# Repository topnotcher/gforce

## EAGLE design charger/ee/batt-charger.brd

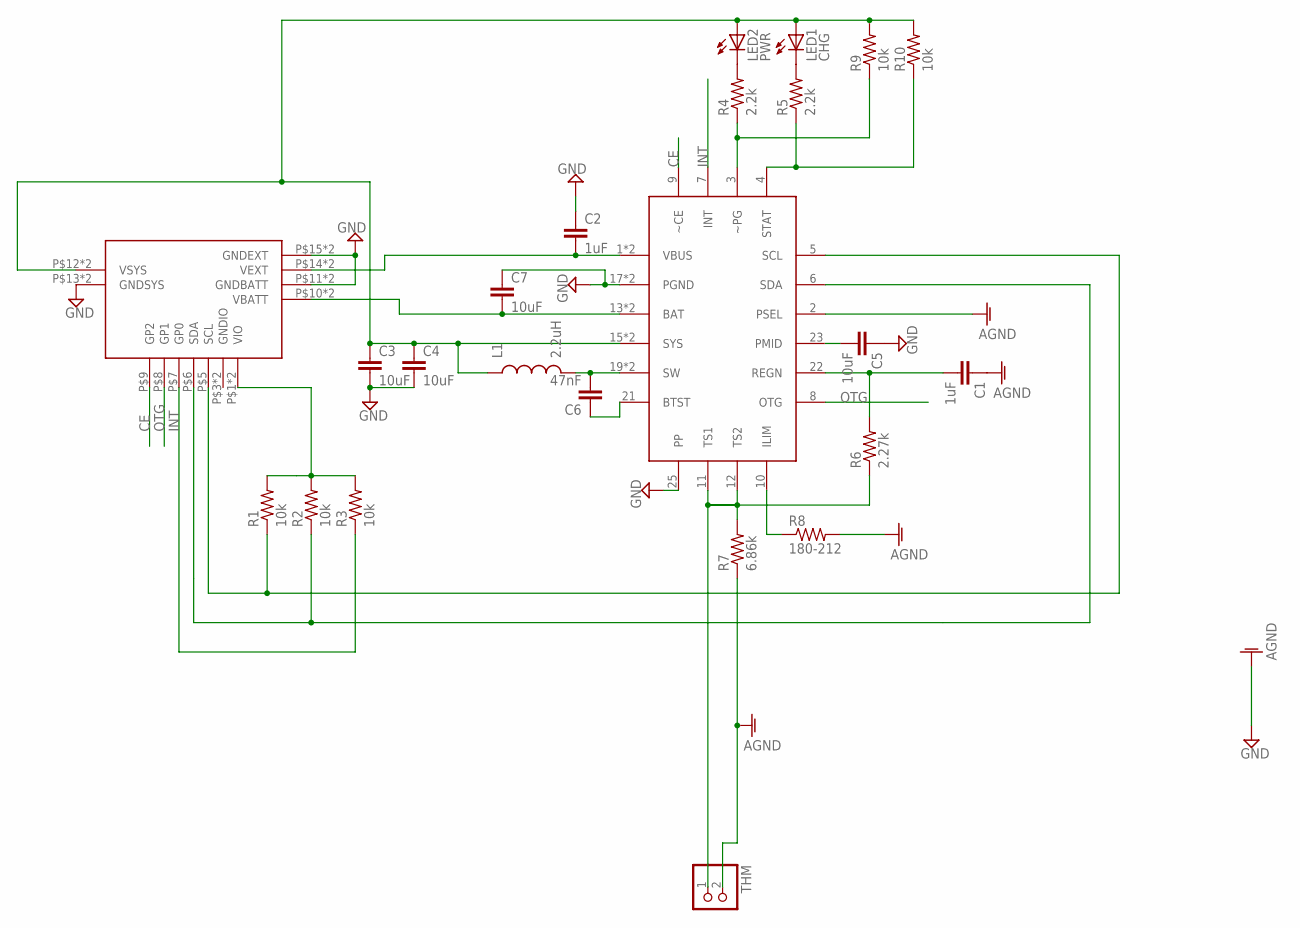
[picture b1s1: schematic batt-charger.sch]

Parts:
C1, C2: 1uF; 0603-CAP
C3, C4, C5, C7: 10uF; 1206
C6: 47nF; 0603-CAP
L1: 2.2uH; INDUCTOR-2020
LED1: CHG; CHIP-LED0603
LED2: PWR; CHIP-LED0603
R1, R2, R3, R9, R10: 10k; R0603
R4, R5: 2.2k; R0603
R6: 2.27k; R0603
R7: 6.86k; R0603
R8: 180-212; R0603
THM: JST_2PIN-THM; JST-PH-2-THM
U$1: BQ24193; QFN-400X400X100-25P
U$2: G4-CHG-SOCKETSTD; G4-CHG-SOCKET

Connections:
AGND: C1.1, R7.1, R8.2, THM.2 (1), U$1.2 (PSEL)
CE: U$1.9 (~CE), U$2.P$9 (GP2)
GND: C2.1, C3.2, C4.2, C5.1, C7.1, U$1.17 (PGND), U$1.18 (PGND), U$1.25 (PP), U$2.P$11 (GNDBATT), U$2.P$13 (GNDSYS), U$2.P$15 (GNDEXT), U$2.P$17 (GNDBATT), U$2.P$19 (GNDSYS), U$2.P$21 (GNDEXT)
INT: R3.1, U$1.7 (INT), U$2.P$7 (GP0)
unnamed: C6.2, L1.P$2 (2), U$1.19 (SW), U$1.20 (SW)
unnamed: R1.1, U$1.5 (SCL), U$2.P$5 (SCL)
unnamed: R2.1, U$1.6 (SDA), U$2.P$6 (SDA)
unnamed: C6.1, U$1.21 (BTST)
unnamed: LED2.C, R4.2
unnamed: LED1.C, R5.2
unnamed: R4.1, R9.1, U$1.3 (~PG)
unnamed: R5.1, R10.1, U$1.4 (STAT)
unnamed: C1.2, R6.2, U$1.22 (REGN)
unnamed: R6.1, R7.2, THM.1 (2), U$1.11 (TS1), U$1.12 (TS2)
unnamed: R8.1, U$1.10 (ILIM)
unnamed: C5.2, U$1.23 (PMID)
OTG: U$1.8 (OTG), U$2.P$8 (GP1)
VBATT: C7.2, U$1.13 (BAT), U$1.14 (BAT), U$2.P$10 (VBATT), U$2.P$16 (VBATT)
VEXT: C2.2, U$1.1 (VBUS), U$1.24 (VBUS), U$2.P$14 (VEXT), U$2.P$20 (VEXT)
VIO: R1.2, R2.2, R3.2, U$2.P$1 (VIO), U$2.P$2 (VIO)
VSYS: C3.1, C4.1, L1.P$1 (1), LED1.A, LED2.A, R9.2, R10.2, U$1.15 (SYS), U$1.16 (SYS), U$2.P$12 (VSYS), U$2.P$18 (VSYS)

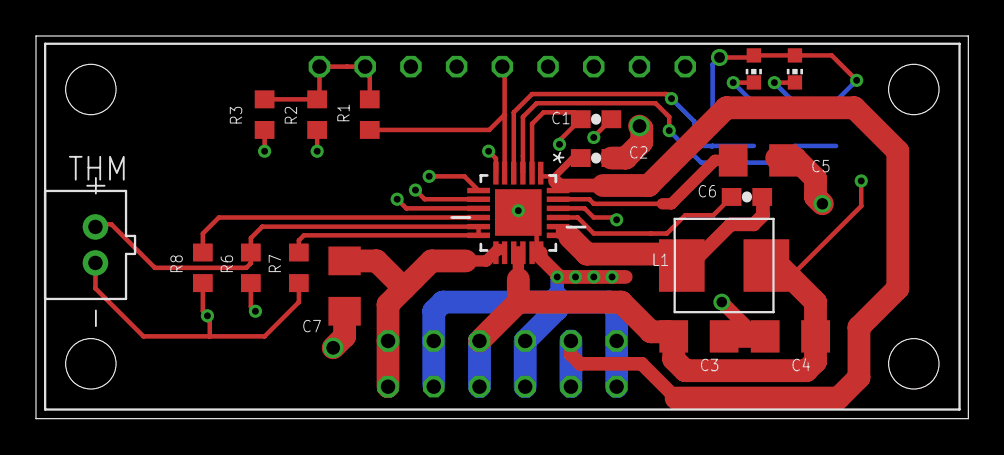
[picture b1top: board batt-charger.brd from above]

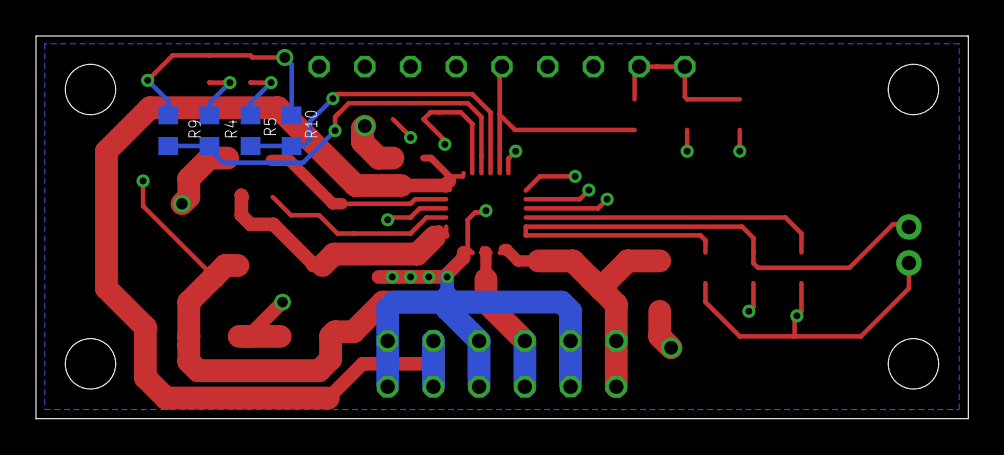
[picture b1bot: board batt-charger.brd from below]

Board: 4 copper layers, 51.8 x 21.3 mm, 23 parts (4 on the bottom side), 21 nets.

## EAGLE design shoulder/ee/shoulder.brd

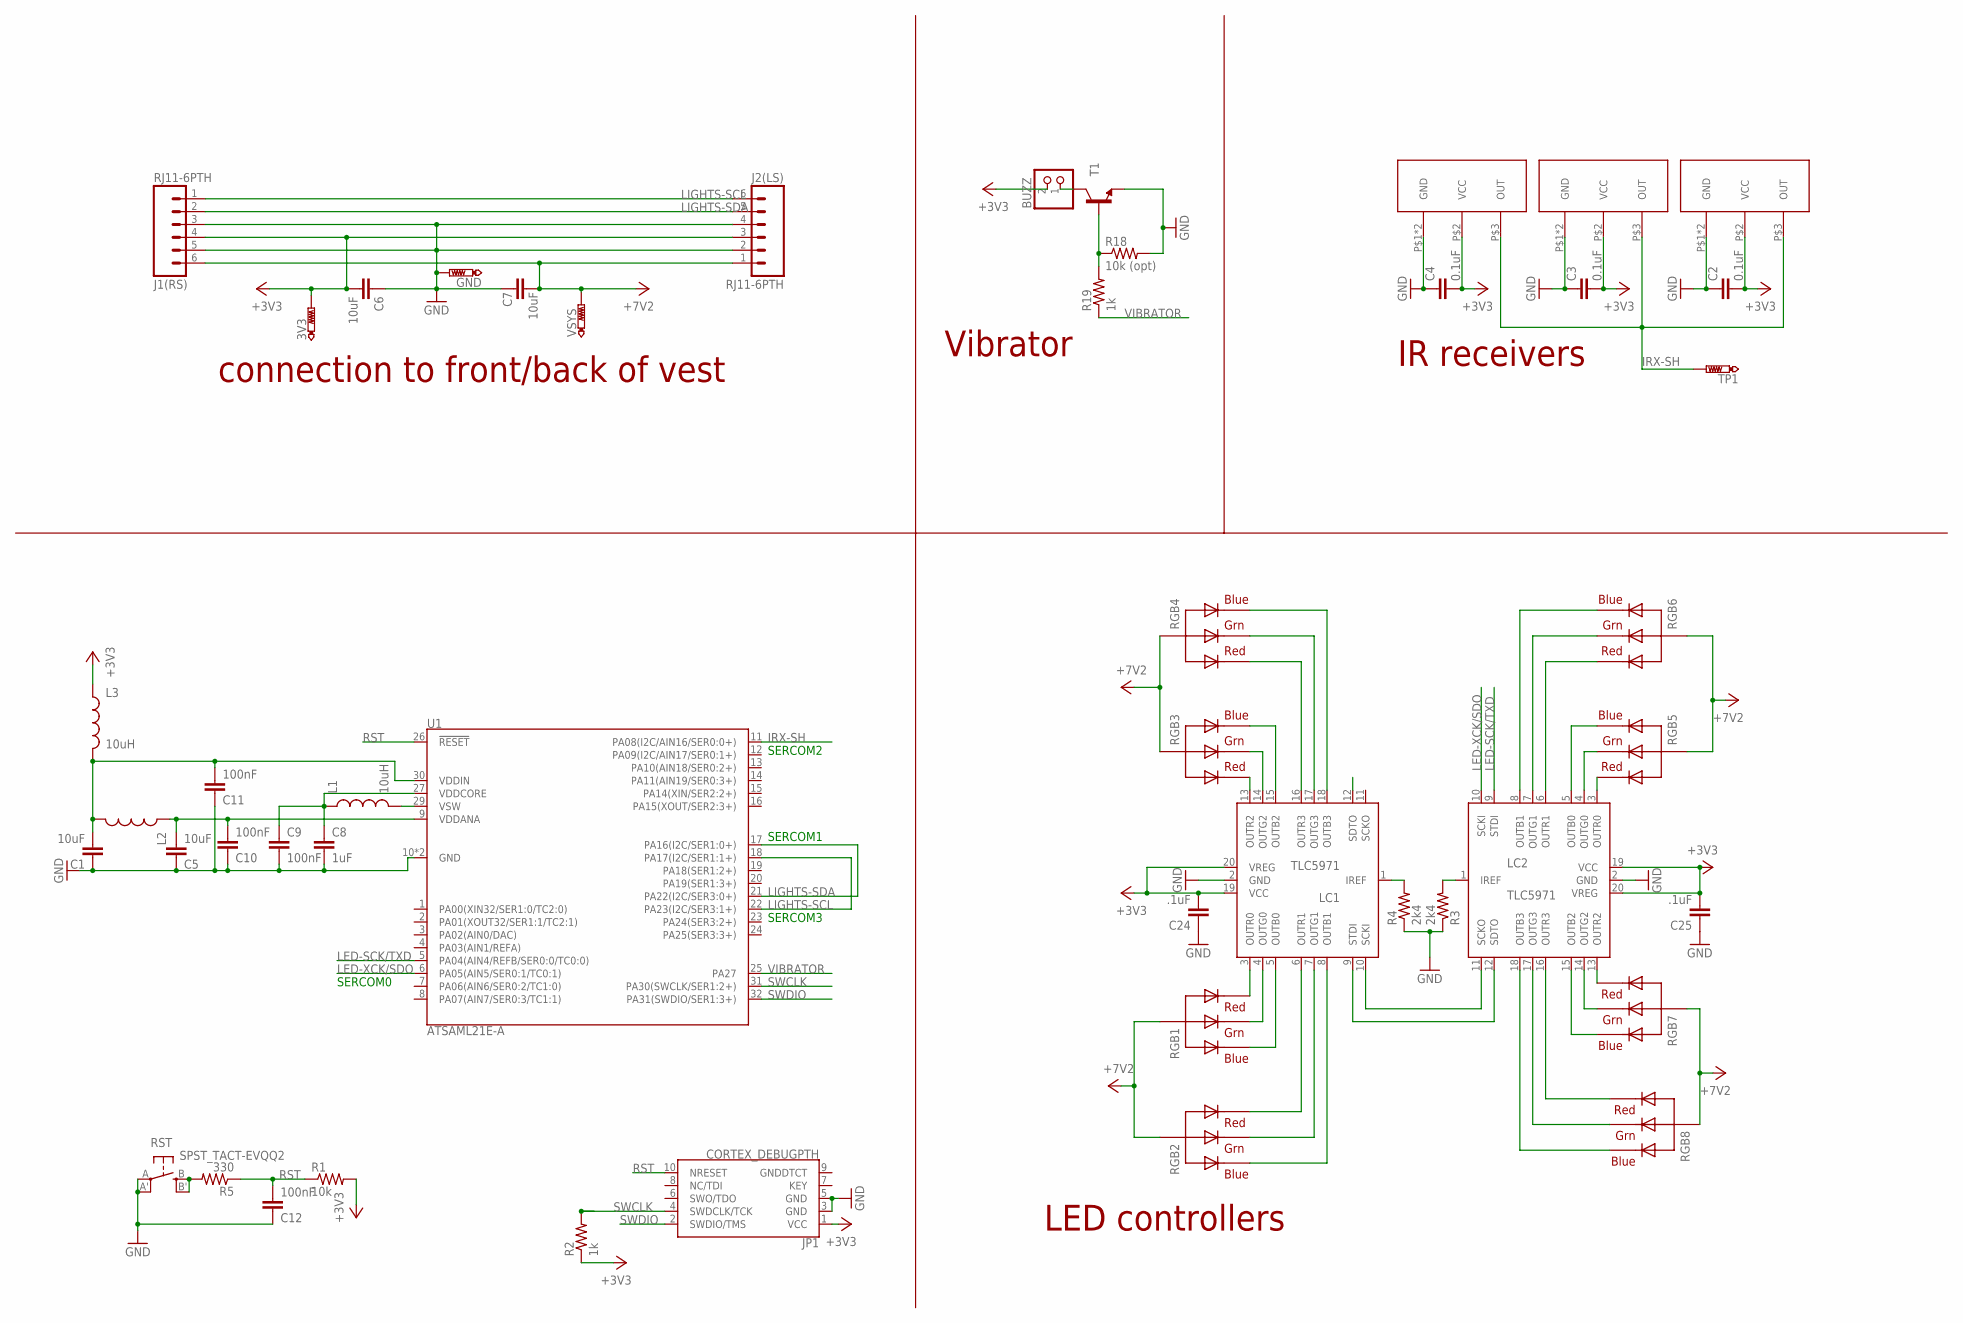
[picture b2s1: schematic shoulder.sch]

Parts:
3V3: PTR1PAD1-17; P1-17
BUZZ: JST_2PIN-THM; JST-PH-2-THM
C1, C5: 10uF; 0603-CAP
C2, C3, C4: 0.1uF; 0603-CAP
C6, C7: 10uF; 1206
C8: 1uF; 0603-CAP
C9, C10, C11, C12: 100nF; 0603-CAP
C24, C25: .1uF; 0603-CAP
GND: PTR1PAD1-17; P1-17
J1(RS), J2(LS): RJ11-6PTH; RJ11-6
JP1: CORTEX_DEBUGPTH; 2X5-PTH-1.27MM
L1, L3: 10uH; 0805
L2: INDUCTOR0603; 0603
LC1, LC2: TLC5971; SSOP20
R1: 10k; 0603-RES
R2, R19: 1k; 0603-RES
R3, R4: 2k4; 0603-RES
R5: 330; 0603-RES
R18: 10k (opt); 0603-RES
RGB1, RGB2, RGB3, RGB4, RGB5, RGB6, RGB7, RGB8: AVAGO-RGB-SMT; AVAGO-SMT-RGB
RST: SPST_TACT-EVQQ2; EVQ-Q2
T1: TRANSISTOR_NPNSOT23; SOT23
TP1: PTR1PAD1-17; P1-17
U1: ATSAML21E-A; TQFP-32-7X7-0.8MM
U$1, U$2: TSMP77000SIDE; TSMP77000
U$3: TSMP77000UP; HEIMDALL-UP
VSYS: PTR1PAD1-17; P1-17

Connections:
+3V3: 3V3.TP, BUZZ.2 (1), C2.2, C3.2, C4.2, C6.2, C24.2, C25.2, J1(RS).4, J2(LS).3, JP1.1 (VCC), L3.1, LC1.19 (VCC), LC1.20 (VREG), LC2.19 (VCC), LC2.20 (VREG), R1.2, R2.1, U$1.P$2 (VCC), U$2.P$2 (VCC), U$3.P$2 (VCC)
+7V2: C7.2, J1(RS).6, J2(LS).1, RGB1.P$4 (VCC), RGB1.P$5 (VCC), RGB1.P$6 (VCC), RGB2.P$4 (VCC), RGB2.P$5 (VCC), RGB2.P$6 (VCC), RGB3.P$4 (VCC), RGB3.P$5 (VCC), RGB3.P$6 (VCC), RGB4.P$4 (VCC), RGB4.P$5 (VCC), RGB4.P$6 (VCC), RGB5.P$4 (VCC), RGB5.P$5 (VCC), RGB5.P$6 (VCC), RGB6.P$4 (VCC), RGB6.P$5 (VCC), RGB6.P$6 (VCC), RGB7.P$4 (VCC), RGB7.P$5 (VCC), RGB7.P$6 (VCC), RGB8.P$4 (VCC), RGB8.P$5 (VCC), RGB8.P$6 (VCC), VSYS.TP
GND: C1.1, C2.1, C3.1, C4.1, C5.1, C6.1, C7.1, C8.2, C9.2, C10.1, C11.1, C12.1, C24.1, C25.1, GND.TP, J1(RS).3, J1(RS).5, J2(LS).2, J2(LS).4, JP1.3 (GND), JP1.5 (GND), LC1.2 (GND), LC2.2 (GND), R3.1, R4.1, R18.2, RST.A, RST.A' (P1), T1.2 (E), U1.10 (GND), U1.28 (GND), U$1.P$1 (GND), U$1.P$4 (GND), U$2.P$1 (GND), U$2.P$4 (GND), U$3.P$1 (GND), U$3.P$4 (GND)
IRX-SH: TP1.TP, U1.11 (PA08(I2C/AIN16/SER0:0+)), U$1.P$3 (OUT), U$2.P$3 (OUT), U$3.P$3 (OUT)
LED-SCK/TXD: LC2.9 (STDI), U1.5 (PA04(AIN4/REFB/SER0:0/TC0:0))
LED-XCK/SDO: LC2.10 (SCKI), U1.6 (PA05(AIN5/SER0:1/TC0:1))
LIGHTS-SCL: J1(RS).1, J2(LS).6, U1.18 (PA17(I2C/SER1:1+)), U1.22 (PA23(I2C/SER3:1+))
LIGHTS-SDA: J1(RS).2, J2(LS).5, U1.17 (PA16(I2C/SER1:0+)), U1.21 (PA22(I2C/SER3:0+))
unnamed: LC1.10 (SCKI), LC2.11 (SCKO)
unnamed: LC1.9 (STDI), LC2.12 (SDTO)
unnamed: C5.2, C10.2, L2.1, U1.9 (VDDANA)
unnamed: C1.2, C11.2, L2.2, L3.2, U1.30 (VDDIN)
unnamed: R5.2, RST.B (S), RST.B' (S1)
unnamed: L1.2, U1.29 (VSW)
unnamed: LC1.3 (OUTR0), RGB1.P$3 (RED)
unnamed: LC2.3 (OUTR0), RGB5.P$3 (RED)
unnamed: LC2.6 (OUTR1), RGB6.P$3 (RED)
unnamed: C8.1, C9.1, L1.1, U1.27 (VDDCORE)
unnamed: BUZZ.1 (2), T1.3 (C)
unnamed: LC1.15 (OUTB2), RGB3.P$1 (BLUE)
unnamed: R18.1, R19.2, T1.1 (B)
unnamed: LC1.13 (OUTR2), RGB3.P$3 (RED)
unnamed: LC1.14 (OUTG2), RGB3.P$2 (GREEN)
unnamed: LC1.16 (OUTR3), RGB4.P$3 (RED)
unnamed: LC1.17 (OUTG3), RGB4.P$2 (GREEN)
unnamed: LC1.18 (OUTB3), RGB4.P$1 (BLUE)
unnamed: LC1.4 (OUTG0), RGB1.P$2 (GREEN)
unnamed: LC1.5 (OUTB0), RGB1.P$1 (BLUE)
unnamed: LC1.6 (OUTR1), RGB2.P$3 (RED)
unnamed: LC1.7 (OUTG1), RGB2.P$2 (GREEN)
unnamed: LC1.8 (OUTB1), RGB2.P$1 (BLUE)
unnamed: LC2.4 (OUTG0), RGB5.P$2 (GREEN)
unnamed: LC2.5 (OUTB0), RGB5.P$1 (BLUE)
unnamed: LC2.7 (OUTG1), RGB6.P$2 (GREEN)
unnamed: LC2.8 (OUTB1), RGB6.P$1 (BLUE)
unnamed: LC2.16 (OUTR3), RGB8.P$3 (RED)
unnamed: LC2.17 (OUTG3), RGB8.P$2 (GREEN)
unnamed: LC2.18 (OUTB3), RGB8.P$1 (BLUE)
unnamed: LC2.15 (OUTB2), RGB7.P$1 (BLUE)
unnamed: LC2.14 (OUTG2), RGB7.P$2 (GREEN)
unnamed: LC2.13 (OUTR2), RGB7.P$3 (RED)
unnamed: LC1.1 (IREF), R4.2
unnamed: LC2.1 (IREF), R3.2
RST: C12.2, JP1.10 (NRESET), R1.1, R5.1, U1.26 (!RESET!)
SWCLK: JP1.4 (SWDCLK/TCK), R2.2, U1.31 (PA30(SWCLK/SER1:2+))
SWDIO: JP1.2 (SWDIO/TMS), U1.32 (PA31(SWDIO/SER1:3+))
VIBRATOR: R19.1, U1.25 (PA27)

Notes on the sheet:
connection to front/back of vest
IR receivers
Vibrator
LED controllers
SERCOM0
SERCOM3
SERCOM1
SERCOM2

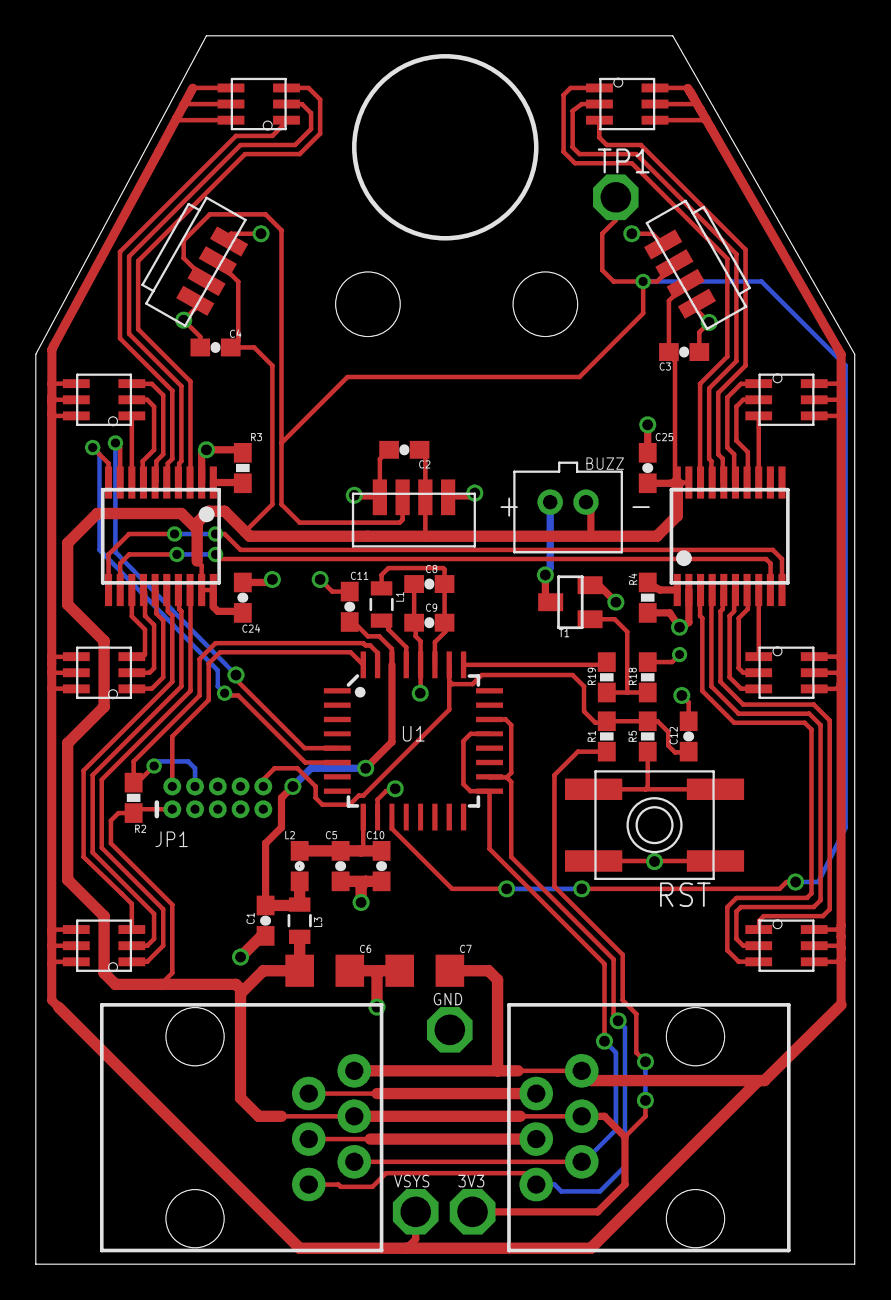
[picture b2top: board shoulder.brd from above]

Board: 2 copper layers, 45.7 x 68.6 mm, 48 parts (0 on the bottom side), 47 nets.

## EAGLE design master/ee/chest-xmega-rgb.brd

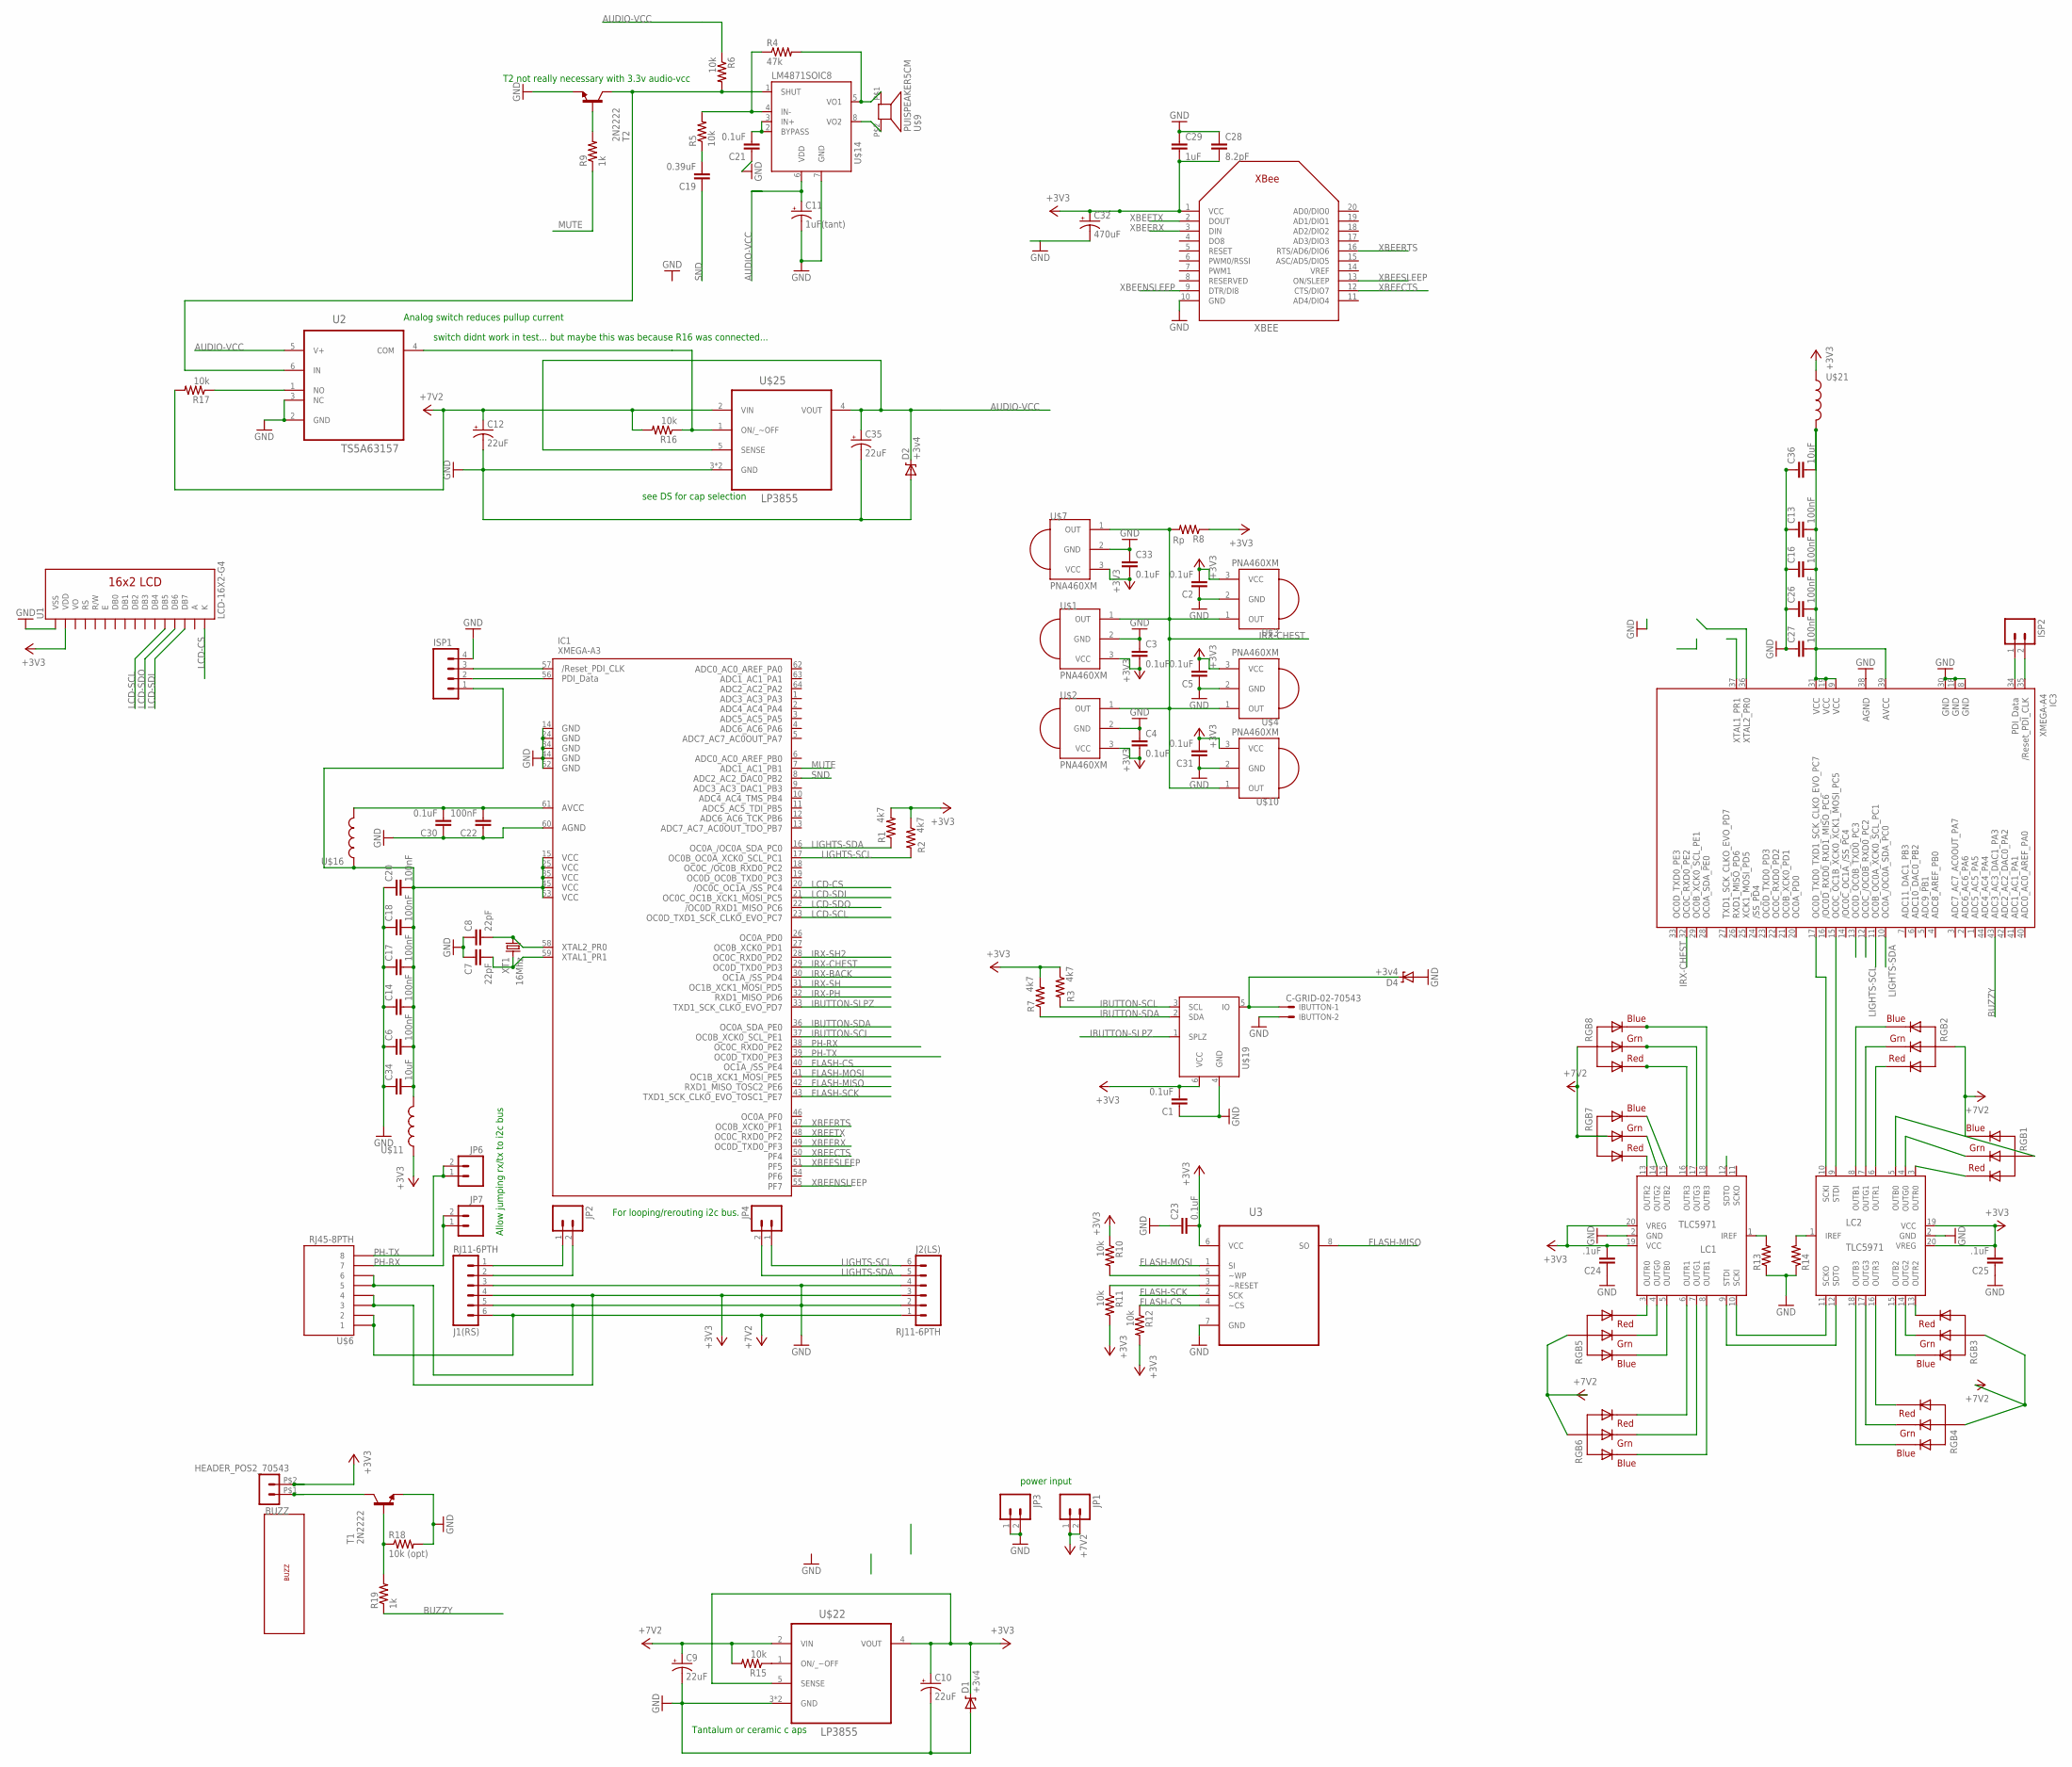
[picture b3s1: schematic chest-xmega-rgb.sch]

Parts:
BUZZ: HEADER_POS2_70543; 70543-POS2
C1, C23, C30: 0.1uF; 0603-CAP
C2, C3, C4, C5, C21, C31, C33: 0.1uF; CAP-PTH-SMALL
C6, C13, C14, C16, C17, C18, C20, C22, C26, C27: 100nF; 0603-CAP
C7, C8: 22pF; CAP-PTH-SMALL
C9, C10, C12, C35: 22uF; EIA3216
C11: 1uF(tant); EIA3216
C19: 0.39uF; CAP-PTH-SMALL
C24, C25: .1uF; CAP-PTH-SMALL
C28: 8.2pF; 0603-CAP
C29: 1uF; 0603-CAP
C32: 470uF; PANASONIC_E
C34, C36: 10uF; 1206
D1, D2, D4: +3v4; DIODE-ZENER
IBUTTON: C-GRID-02-70543; 70543-02
IC1: XMEGA-A3; TQFP64
IC3: XMEGA-A4; TQFP44
ISP1: M04LOCK; 1X04_LOCK
ISP2: M02LOCK; 1X02_LOCK
J1(RS), J2(LS): RJ11-6PTH; RJ11-6
JP1, JP3: M023.5MM; SCREWTERMINAL-3.5MM-2
JP2, JP4, JP6, JP7: M02LOCK; 1X02_LOCK
LC1, LC2: TLC5971; SSOP20
R1, R2, R3, R7: 4k7; 0204/7
R4: 47k; 0204/7
R5, R6, R15, R16, R17: 10k; 0204/7
R8: Rp; 0204/7
R9, R19: 1k; 0204/7
R10, R11, R12: 10k; 0805
R13, R14: R-US_0204/7; 0204/7
R18: 10k (opt); 0204/7
RGB1, RGB2, RGB3, RGB4, RGB5, RGB6, RGB7, RGB8: AVAGO-RGB-SMT; AVAGO-SMT-RGB
T1, T2: 2N2222; TO92-EBC-OVAL
U1: LCD-16X2-G4
U2: TS5A63157; SOT65P210X110-6N
U3: AT45DB321D-SU; SOIC127P798X216-8N
U$1, U$2, U$3, U$4, U$7, U$10: PNA460XM
U$6: RJ45-8PTH; RJ45-8
U$9: PUISPEAKER5CM; PUI-AS05008MR-4-R
U$11, U$16, U$21: INDUCTOR1206H*; 1206
U$13: VIB-CAPSULE
U$14: LM4871SOIC8; SOIC8
U$19: DS2483-SOT23-6; SOT23-6
U$22, U$25: LP3855; TO-263-5
XBEE: XBEE-WIFIXBEE; XBEE-WIFI
XT1: 16Mhz; HC49US

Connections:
+3V3: BUZZ.P$2 (2), C1.2, C2.2, C3.2, C4.2, C5.2, C10.A (+), C23.2, C24.2, C25.2, C28.2, C29.2, C31.2, C32.+, C33.2, D1.P$1 (C), J1(RS).4, J2(LS).3, LC1.19 (VCC), LC1.20 (VREG), LC2.19 (VCC), LC2.20 (VREG), R1.2, R2.1, R3.1, R7.2, R8.1, R10.1, R11.2, R12.2, U1.2 (VDD), U3.6 (VCC), U$1.3 (VCC), U$2.3 (VCC), U$3.3 (VCC), U$4.3 (VCC), U$6.3, U$6.4, U$7.3 (VCC), U$10.3 (VCC), U$11.1, U$19.6 (VCC), U$21.1, U$22.4 (VOUT), U$22.5 (SENSE), XBEE.1 (VCC)
+7V2: C9.A (+), C12.A (+), J1(RS).6, J2(LS).1, JP1.1, JP1.2, R15.2, R16.2, R17.2, RGB1.P$4 (VCC), RGB1.P$5 (VCC), RGB1.P$6 (VCC), RGB2.P$4 (VCC), RGB2.P$5 (VCC), RGB2.P$6 (VCC), RGB4.P$4 (VCC), RGB4.P$5 (VCC), RGB4.P$6 (VCC), RGB5.P$4 (VCC), RGB5.P$5 (VCC), RGB5.P$6 (VCC), RGB6.P$4 (VCC), RGB6.P$5 (VCC), RGB6.P$6 (VCC), RGB7.P$4 (VCC), RGB7.P$5 (VCC), RGB7.P$6 (VCC), RGB8.P$4 (VCC), RGB8.P$5 (VCC), RGB8.P$6 (VCC), U$6.1, U$6.2, U$22.2 (VIN), U$25.2 (VIN)
A: U1.15 (A)
AUDIO-VCC: C11.A (+), C35.A (+), D2.P$1 (C), R6.1, U2.5 (V+), U$14.6 (VDD), U$25.4 (VOUT), U$25.5 (SENSE)
BUZZY: IC3.43 (PA3), R19.1
FLASH-CS: IC1.40 (PE4), R12.1, U3.4 (~CS)
FLASH-MISO: IC1.42 (PE6), U3.8 (SO)
FLASH-MOSI: IC1.41 (PE5), U3.1 (SI)
FLASH-SCK: IC1.43 (PE7), U3.2 (SCK)
GND: C1.1, C2.1, C3.1, C4.1, C5.1, C6.1, C7.1, C8.1, C9.C (-), C10.C (-), C11.C (-), C12.C (-), C13.1, C14.1, C16.1, C17.1, C18.1, C20.1, C21.1, C22.1, C23.1, C24.1, C25.1, C26.1, C27.1, C28.1, C29.1, C30.1, C31.1, C32.-, C33.1, C34.1, C35.C (-), C36.1, D1.P$2 (A), D2.P$2 (A), D4.P$2 (A), IBUTTON.2, IC1.14 (GND1), IC1.24 (GND2), IC1.34 (GND3), IC1.44 (GND4), IC1.52 (GND5), IC1.60 (AGND), IC3.8 (GND1), IC3.18 (GND2), IC3.30 (GND3), IC3.38 (AGND), ISP1.4, J1(RS).3, J1(RS).5, J2(LS).2, J2(LS).4, JP3.1, JP3.2, LC1.2 (GND), LC2.2 (GND), R13.1, R14.1, R18.2, T1.E, T2.E, U1.1 (VSS), U2.2 (GND), U2.3 (NC), U3.7 (GND), U$1.2 (GND), U$2.2 (GND), U$3.2 (GND), U$4.2 (GND), U$6.5, U$6.6, U$7.2 (GND), U$10.2 (GND), U$14.7 (GND), U$19.4 (GND), U$22.3 (GND), U$22.TAB (GND), U$25.3 (GND), U$25.TAB (GND), XBEE.10 (GND)
IBUTTON-SCL: IC1.37 (PE1), R3.2, U$19.3 (SCL)
IBUTTON-SDA: IC1.36 (PE0), R7.1, U$19.2 (SDA)
IBUTTON-SLPZ: IC1.33 (PD7), U$19.1 (SPLZ)
IRX-BACK: IC1.30 (PD4)
IRX-CHEST: IC1.29 (PD3), IC3.32 (PE2), R8.2, U$1.1 (OUT), U$2.1 (OUT), U$3.1 (OUT), U$4.1 (OUT), U$7.1 (OUT), U$10.1 (OUT)
IRX-PH: IC1.32 (PD6)
IRX-SH: IC1.31 (PD5)
IRX-SH2: IC1.28 (PD2)
LCD-CS: IC1.20 (PC4), U1.16 (K)
LCD-SCL: IC1.23 (PC7), U1.12 (DB5)
LCD-SDI: IC1.21 (PC5), U1.14 (DB7)
LCD-SDO: IC1.22 (PC6), U1.13 (DB6)
LIGHTS-SCL: IC1.17 (PC1), IC3.11 (PC1), J2(LS).6, JP4.1, R2.2
LIGHTS-SDA: IC1.16 (PC0), IC3.10 (PC0), J2(LS).5, JP4.2, R1.1
MUTE: IC1.7 (PB1), R9.1
unnamed: LC1.10 (SCKI), LC2.11 (SCKO)
unnamed: LC1.9 (STDI), LC2.12 (SDTO)
unnamed: IC3.15 (PC5), LC2.9 (STDI)
unnamed: IC3.17 (PC7), LC2.10 (SCKI)
unnamed: IC3.34 (PDI_DATA), ISP2.1
unnamed: IC3.35 (RESET), ISP2.2
unnamed: IC1.57 (RESET), ISP1.3
unnamed: IC1.56 (PDI_DATA), ISP1.2
unnamed: C7.2, IC1.59 (PR1), XT1.2
unnamed: C6.2, C14.2, C17.2, C18.2, C20.2, C34.2, IC1.15 (VCC1), IC1.25 (VCC2), IC1.35 (VCC3), IC1.45 (VCC4), IC1.53 (VCC5), ISP1.1, U$11.2, U$16.1
unnamed: C13.2, C16.2, C26.2, C27.2, C36.2, IC3.9 (VCC1), IC3.19 (VCC2), IC3.31 (VCC3), IC3.39 (AVCC), U$21.2
unnamed: J1(RS).1, JP2.1
unnamed: C8.2, IC1.58 (PR0), XT1.1
unnamed: LC1.15 (OUTB2), RGB7.P$1 (BLUE)
unnamed: J1(RS).2, JP2.2
unnamed: R10.2, U3.5 (~WP)
unnamed: R17.1, U2.1 (NO)
unnamed: C22.2, C30.2, IC1.61 (AVCC), U$16.2
unnamed: LC1.13 (OUTR2), RGB7.P$3 (RED)
unnamed: R11.1, U3.3 (~RESET)
unnamed: R4.1, R5.2, U$14.4 (IN-)
unnamed: LC1.14 (OUTG2), RGB7.P$2 (GREEN)
unnamed: D4.P$1 (C), IBUTTON.1, U$19.5 (IO)
unnamed: U$9.P$2 (2), U$14.8 (VO2)
unnamed: R4.2, U$9.P$1 (1), U$14.5 (VO1)
unnamed: LC1.16 (OUTR3), RGB8.P$3 (RED)
unnamed: LC1.17 (OUTG3), RGB8.P$2 (GREEN)
unnamed: LC1.18 (OUTB3), RGB8.P$1 (BLUE)
unnamed: C19.2, R5.1
unnamed: LC1.3 (OUTR0), RGB5.P$3 (RED)
unnamed: LC1.4 (OUTG0), RGB5.P$2 (GREEN)
unnamed: LC1.5 (OUTB0), RGB5.P$1 (BLUE)
unnamed: LC1.6 (OUTR1), RGB6.P$3 (RED)
unnamed: LC1.7 (OUTG1), RGB6.P$2 (GREEN)
unnamed: LC1.8 (OUTB1), RGB6.P$1 (BLUE)
unnamed: LC2.3 (OUTR0), RGB1.P$3 (RED)
unnamed: LC2.4 (OUTG0), RGB1.P$2 (GREEN)
unnamed: LC2.5 (OUTB0), RGB1.P$1 (BLUE)
unnamed: BUZZ.P$1 (1), T1.C
unnamed: R15.1, U$22.1 (ON/_~OFF)
unnamed: C21.2, U$14.2 (BYPASS), U$14.3 (IN+)
unnamed: R18.1, R19.2, T1.B
unnamed: LC2.6 (OUTR1), RGB2.P$3 (RED)
unnamed: LC2.7 (OUTG1), RGB2.P$2 (GREEN)
unnamed: LC2.8 (OUTB1), RGB2.P$1 (BLUE)
unnamed: LC2.16 (OUTR3), RGB4.P$3 (RED)
unnamed: LC2.17 (OUTG3), RGB4.P$2 (GREEN)
unnamed: LC2.18 (OUTB3), RGB4.P$1 (BLUE)
unnamed: LC2.15 (OUTB2), RGB3.P$1 (BLUE)
unnamed: LC2.14 (OUTG2), RGB3.P$2 (GREEN)
unnamed: LC2.13 (OUTR2), RGB3.P$3 (RED)
unnamed: R6.2, T2.C, U2.6 (IN), U$14.1 (SHUT)
unnamed: LC1.1 (IREF), R13.2
unnamed: LC2.1 (IREF), R14.2
unnamed: R9.2, T2.B
unnamed: R16.1, U2.4 (COM), U$25.1 (ON/_~OFF)
PH-RX: IC1.38 (PE2), JP7.1, JP7.2, U$6.7
PH-TX: IC1.39 (PE3), JP6.1, JP6.2, U$6.8
SND: C19.1, IC1.8 (PB2)
XBEECTS: IC1.50 (PF4), XBEE.12 (CTS/DIO7)
XBEENSLEEP: IC1.55 (PF7), XBEE.9 (DTR/DI8)
XBEERTS: IC1.47 (PF1), XBEE.16 (RTS/AD6/DIO6)
XBEERX: IC1.49 (PF3), XBEE.3 (DIN)
XBEESLEEP: IC1.51 (PF5), XBEE.13 (ON/SLEEP)
XBEETX: IC1.48 (PF2), XBEE.2 (DOUT)

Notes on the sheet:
For looping/rerouting i2c bus.
Allow jumping rx/tx to i2c bus
power input
Tantalum or ceramic c aps
Analog switch reduces pullup current
T2 not really necessary with 3.3v audio-vcc
switch didnt work in test... but maybe this was because R16 was connected...
see DS for cap selection

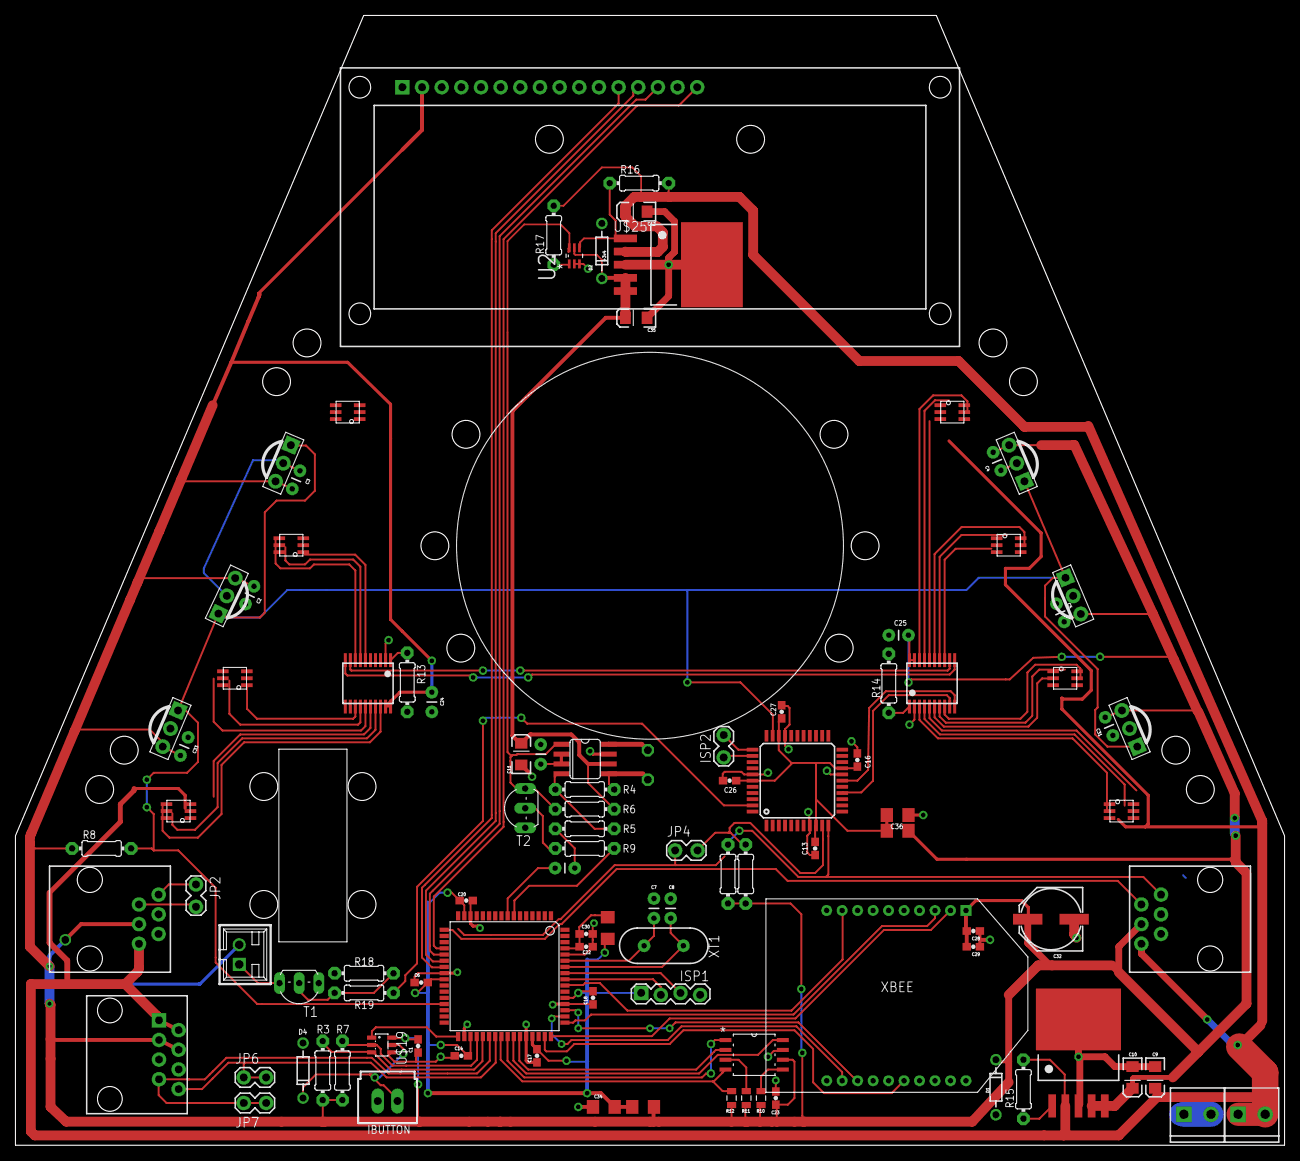
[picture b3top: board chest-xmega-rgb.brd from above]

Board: 2 copper layers, 164.0 x 146.0 mm, 104 parts (0 on the bottom side), 85 nets.

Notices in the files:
parts and their libraries:
SparkFun-Capacitors: Licensing: CC v3.0 Share-Alike You are welcome to use this library for commercial purposes.
